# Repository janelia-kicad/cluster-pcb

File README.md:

- [Repository Info](#orgbacf8f6)
- [Images](#org53d800a)
- [Schematic](#org38f91d3)
- [PCB](#org650b85d)
- [Bill of Materials](#org1cf7621)
- [Development](#org0d98822)

    <!-- This file is generated automatically from metadata -->
    <!-- File edits may be overwritten! -->

# Repository Info

-   Project Name: cluster-pcb
-   Synopsis: PCB for each cluster of prisms in the Voigts Lab honeycomb maze.
-   Documentation Version: 2.1.0
-   Pcb Version: 2.1
-   Enclosure Version: 1.0
-   Supplemental BOM Version: 2.1.0
-   Release Date: 2025-05-23
-   Creation Date: 2024-06-28
-   Kicad Version: 9.0
-   License: BSD-3-Clause
-   URL: <https://github.com/janelia-kicad/cluster-pcb>
-   Author: Peter Polidoro
-   Email: peter@polidoro.io
-   Copyright: 2025 Howard Hughes Medical Institute
-   References:
    -   <https://github.com/janelia-kicad/prism-pcb>
    -   [W5500-EVB-Pico](https://docs.wiznet.io/Product/iEthernet/W5500/w5500-evb-pico)

# Images

# Schematic

[./documentation/schematic/cluster-pcb.pdf](./documentation/schematic/cluster-pcb.pdf)

# PCB

# Bill of Materials

## Board

| Item | Synopsis                                  | Manufacturer Part Number | Manufacturer                         | Quantity | Reference(s)                                                                                                                    | Package            |
|---- |----------------------------------------- |------------------------ |------------------------------------ |-------- |------------------------------------------------------------------------------------------------------------------------------- |------------------ |
| 1    | 50V 3.3uF                                 | FS32X335K500EGG          | PSA(Prosperity Dielectrics)          | 1        | C301                                                                                                                            | 1210               |
| 2    | CAP CER 0.1UF 100V X5R                    | GRM155R62A104KE14D       | Murata Electronics                   | 24       | C302 C501 C502 C504 C601 C602 C604 C701 C702 C704 C801 C802 C804 C901 C902 C904 C1001 C1002 C1004 C1101 C1102 C1104 C1201 C1202 | 0402               |
| 3    | CAP CER 1UF 25V X5R                       | GRT155R61E105KE01D       | Murata Electronics                   | 2        | C303 C304                                                                                                                       | 0402               |
| 4    | CAP CER 47UF 10V X5R                      | CGA0805X5R476M100MT      | HRE                                  | 1        | C305                                                                                                                            | 0805               |
| 5    | CAP CER 27pF 50V 5%                       | 0402CG270J500NT          | FH (Guangdong Fenghua Advanced Tech) | 7        | C503 C603 C703 C803 C903 C1003 C1103                                                                                            | 0402               |
| 6    | CAP CER 1UF 35V X5R                       | CL05A105KL5NRNC          | Samsung Electro-Mechanics            | 1        | C1401                                                                                                                           | 0402               |
| 7    | CAP CER 0.22UF 25V X6S                    | GRT155C81E224KE01D       | Murata Electronics                   | 3        | C1402 C1403 C1404                                                                                                               | 0402               |
| 8    | 50V 15A PowerDI-5 Super Barrier Rectifier | SBRT15U50SP5-13          | Diodes Incorporated                  | 1        | D301                                                                                                                            | PowerDI-5          |
| 9    | LED RED CLEAR CHIP SMD                    | APHHS1005SURCK           | Kingbright                           | 1        | D302                                                                                                                            | 0402               |
| 10   | DIODE SCHOTTKY 20V 1A                     | MBR120VLSFT1G            | onsemi                               | 8        | D401 D501 D601 D701 D801 D901 D1001 D1101                                                                                       | SOD-123FL          |
| 11   | CMC 22UH 200MA 2LN 1.2KOHM SMD            | ACT45B-220-2P-TL003      | TDK                                  | 7        | FL501 FL601 FL701 FL801 FL901 FL1001 FL1101                                                                                     | 1812               |
| 12   | USB Type-C 2.0 16P 5A                     | GT-USB-7047C             | G-Switch                             | 7        | J501 J601 J701 J801 J901 J1001 J1101                                                                                            | SMD                |
| 13   | RA73F 2A 2K32 0.1% 5K RL                  | RA73F2A2K32BTD           | TE Connectivity Passive Product      | 1        | R301                                                                                                                            | 0805               |
| 14   | RES SMD 1.8K OHM 5% 100mW                 | ERJ2GEJ182X              | PANASONIC                            | 16       | R401 R402 R505 R506 R605 R606 R705 R706 R805 R806 R905 R906 R1005 R1006 R1105 R1106                                             | 0402               |
| 15   | RES SMD 100 OHM 1% 62.5mW                 | 0402WGF1000TCE           | UNI-ROYAL(Uniroyal Elec)             | 7        | R501 R601 R701 R801 R901 R1001 R1101                                                                                            | 0402               |
| 16   | RES SMD 4.7K OHM 1% 6.25mW                | 0402WGF4701TCE           | UNI-ROYAL(Uniroyal Elec)             | 7        | R502 R602 R702 R802 R902 R1002 R1102                                                                                            | 0402               |
| 17   | RES SMD 1.4K OHM 1% 62.5mW                | RC0402FR-071K4L          | YAGEO                                | 7        | R503 R603 R703 R803 R903 R1003 R1103                                                                                            | 0402               |
| 18   | RES SMD 604 OHM 1% 100mW                  | ERJ2RKF6040X             | PANASONIC                            | 7        | R504 R604 R704 R804 R904 R1004 R1104                                                                                            | 0402               |
| 19   | RES SMD 10K OHM 5% 1/10W                  | ERJ2GEJ103X              | PANASONIC                            | 10       | R1201 R1202 R1203 R1204 R1205 R1206 R1207 R1208 R1209 R1210                                                                     | 0402               |
| 20   | RES SMD 40k OHM 1% 100mW                  | SCR0603F40K              | VO                                   | 2        | R1401 R1402                                                                                                                     | 0603               |
| 21   | SPEAKER 8OHM 700MW                        | KLJ-01304T-08R07W        | KELIKING                             | 1        | SP1401                                                                                                                          |                    |
| 22   | SWITCH SLIDE DIP SPST 0.025A 24V          | SDA08H1SBDR              | C&K                                  | 1        | SW1201                                                                                                                          | SMD                |
| 23   | TERM BLOCK HDR 2POS 90DEG 5.08MM          | 1757242                  | Phoenix Contact                      | 1        | T301                                                                                                                            | Push-Pull P=5.08mm |
| 24   | Pulse Transformer 120uH 1CT:1CT           | FB020G00                 | Dongguan Mentech Optical & Magnetic  | 7        | TR501 TR601 TR701 TR801 TR901 TR1001 TR1101                                                                                     | SMD-6P 3.5x3.2mm   |
| 25   | DC-DC 5V 600mA Output 3-65V Input         | TPSM365R6V5RDNR          | Texas Instruments                    | 1        | U301                                                                                                                            | QFN-11(3.5x4.5)    |
| 26   | SPI Isolator                              | LTC6820HMS#3ZZTRPBF      | Analog Devices                       | 7        | U501 U601 U701 U801 U901 U1001 U1101                                                                                            | MSOP-16            |
| 27   | IC BUFF NON-INVERT 1.65-5.5V              | SN74LVC1G125DRYR         | Texas Instruments                    | 7        | U503 U603 U703 U803 U903 U1003 U1103                                                                                            | USON-6(1x1.5)      |
| 28   | IC XPNDR 400KHZ I2C SMBUS                 | TCA6408ARGTR             | Texas Instruments                    | 1        | U1201                                                                                                                           | QFN-16-EP(3x3)     |
| 29   | IC AMP CLASS AB MONO 1.7W                 | TPA6204A1DRBR            | Texas Instruments                    | 1        | U1401                                                                                                                           | QFN-8-EP(3x3)      |
|      | IC PWR DRIVER N-CHAN 1:1                  |                          | Texas Instruments                    | 7        | U502 U602 U702 U802 U902 U1002 U1102                                                                                            | EMSOP-8-EP         |

## Supplemental

| Item | Synopsis                        | Manufacturer Part Number | Manufacturer    | Quantity | Cost  | Total |
|---- |------------------------------- |------------------------ |--------------- |-------- |----- |----- |
| 1    | TERM BLOCK PLUG 2POS STR 5.08MM | 1758364                  | Phoenix Contact | 1        | 1.63  | 1.63  |
| 2    | CONN FERRULE DIN 16AWG BLACK    | 3200043                  | Phoenix Contact | 4        | 0.14  | 0.56  |
| 3    | POWER CABLE BULK SJT 16/3       | H-137                    | GlobTek, Inc.   | 1        | 2.40  | 2.40  |
| 4    | W5100S-EVB-PICO RP2040 W5100S   | W5100S-EVB-PICO          | WIZnet          | 1        | 9.95  | 9.95  |
| 5    | Supplemental BOM Version: 2.1.0 |                          |                 |          | Total | 14.54 |

# Development

## Install Guix

[Install Guix](https://guix.gnu.org/manual/en/html_node/Binary-Installation.html)

## Generate Output from KiCad

### Remove previous versions

```sh
rm -rf ./documentation/3dmodels/* && rm -rf ./documentation/bom/* && rm -rf ./documentation/fabrication/* && rm -rf ./documentation/pcb/* && rm -rf ./documentation/schematic/*pcb
```

### Images

1.  3D Viewer

    Output directory: ../documentation/pcb
    
    -   pcb.png
    -   top.png
    -   bottom.png
    -   front.png
    -   back.png
    -   left.png
    -   right.png

2.  Trim

        make trimmed-images

3.  Schematic PDF

    File -> Plot
    
    Output directory: ../documentation/schematic
    
    Plot All Pages
    
    -   Output format PDF
    -   Page Size = Schematic size
    -   Plot drawing sheet
    -   Output mode = Color
    -   Color theme = KiCad Default
    -   Default line width = 0.006 in

4.  Schematic SVG

    File -> Plot
    
    Output directory: ../documentation/schematic
    
    Plot All Pages
    
    -   Output format SVG
    -   Page Size = Schematic size
    -   Plot drawing sheet
    -   Output mode = Color
    -   Color theme = Solarized Light
    -   Default line width = 0.012 in

5.  PCB SVG

    Add Edge.Cuts, holes, and dimensions to User.Drawings
    
    File -> Plot
    
    Output directory: ../documentation/pcb
    
    -   Plot format SVG
    -   Include Layers
        -   User.Drawings
        -   F.Silkscreen
        -   B.Silkscreen
        -   F.Fab
        -   B.Fab
    -   Plot on All Layers
        -   Edge.Cuts
    -   Plot footprint values
    -   Plot reference designators
    -   SVG Options
        -   Precision = 4
        -   Output mode = color
    
        make cropped-svg

### Fabrication Files

1.  Gerbers

    File -> Fabrication Outputs -> Gerbers (.gbr)
    
    Output directory: ../documentation/fabrication/gerbers
    
    Include Layers:
    
    -   F.Cu
    -   F.Paste
    -   F.Silks
    -   F.Mask
    -   F.Fab
    -   B.Cu
    -   B.Paste
    -   B.Silks
    -   B.Mask
    -   B.Fab
    -   Edge.Cuts - (contain the board outline/cutouts.)
    -   In1.Cu, In2.Cu … - (needed for 4/6 layer designs.)
    
    Options:
    
    -   Select Plot reference designators, otherwise designators will not appear on silkscreen layers.
    -   Select Check zone fills before plotting
    -   Select Use Protel filename extensions, this is recommended as JLCPCB prefers Protel filename extensions.
    -   Select Subtract soldermask from silkscreen, this ensures no silkscreen on pads.
    -   Coordinate format 4.6 unit mm

2.  Drill and Map Files

    Output directory: ../documentation/fabrication/gerbers
    
    Options:
    
    -   Excellon drill file format
    -   Check Use alternate drill mode for "Oval Holes Drill Mode".
    -   Check Absolute for "Drill Origin".
    -   Check Millimeters for "Drill Units".
    -   Check Decimal format for "Zeros Format".
    -   Gerber X2 map file format
    
    Zip gerber files
    
        zip ./documentation/fabrication/gerbers.zip ./documentation/fabrication/gerbers/*

3.  BOM

    Generate BOM from schematic editor using blank command line to create bom xml file.

4.  POS

    File -> Fabrication Outputs -> Component Placement (.pos)
    
    Output directory: ../documentation/fabrication/
    
    Settings:
    
    -   Format = CSV
    -   Units = Millimeters
    -   Files = Single file for board
    -   Do not use drill/place file origin
    
    Modify pos files:
    
    -   Ref -> Designator
    -   PosX -> Mid X
    -   PosY -> Mid Y
    -   Rot -> Rotation
    -   Side -> Layer

5.  Step

    File -> Export -> Step
    
    Output directory: ../documentation/3dmodels/pcb.step
    
    -   Drill/place file origin
    -   Overwrite old file
    -   Standard Board outline chaining tolerance

## Edit metadata.org

    make metadata-edits

## Tangle metadata.org

    make metadata

## Edit project

    make kicad-edits
    exit

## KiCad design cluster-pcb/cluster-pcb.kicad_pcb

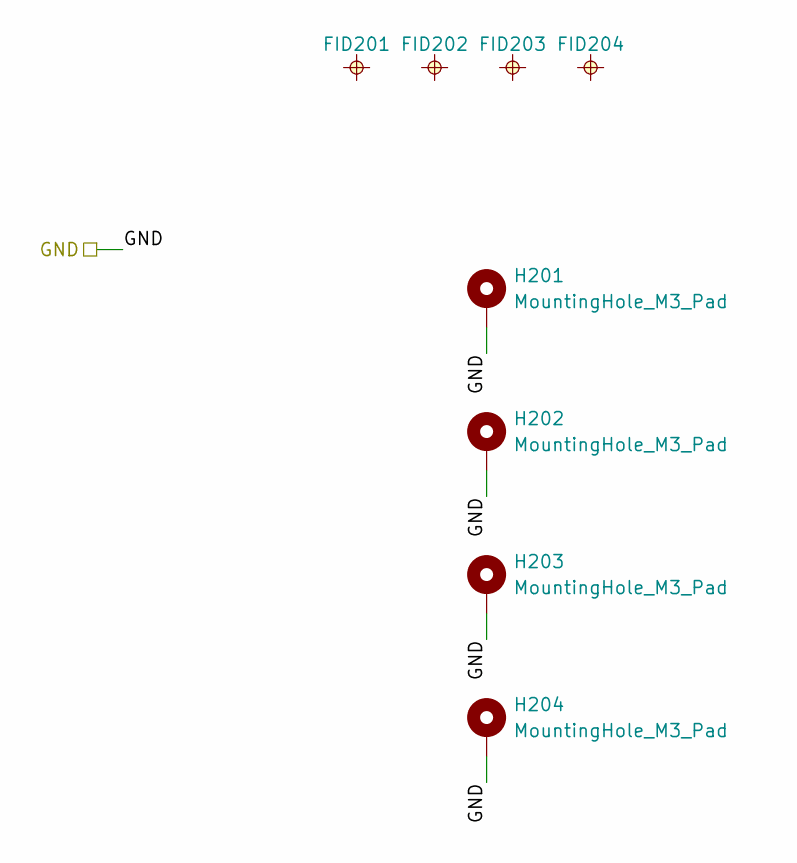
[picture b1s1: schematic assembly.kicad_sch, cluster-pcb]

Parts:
FID201, FID202, FID203, FID204: FIDUCIAL_0.5mm_MASK1mm; FIDUCIAL_0.5mm_Mask1mm
H201, H202, H203, H204: MountingHole_M3_Pad; MountingHole_3.2mm_M3_Pad

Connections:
/GND: H201.1, H202.1, H203.1, H204.1; also elsewhere on the board

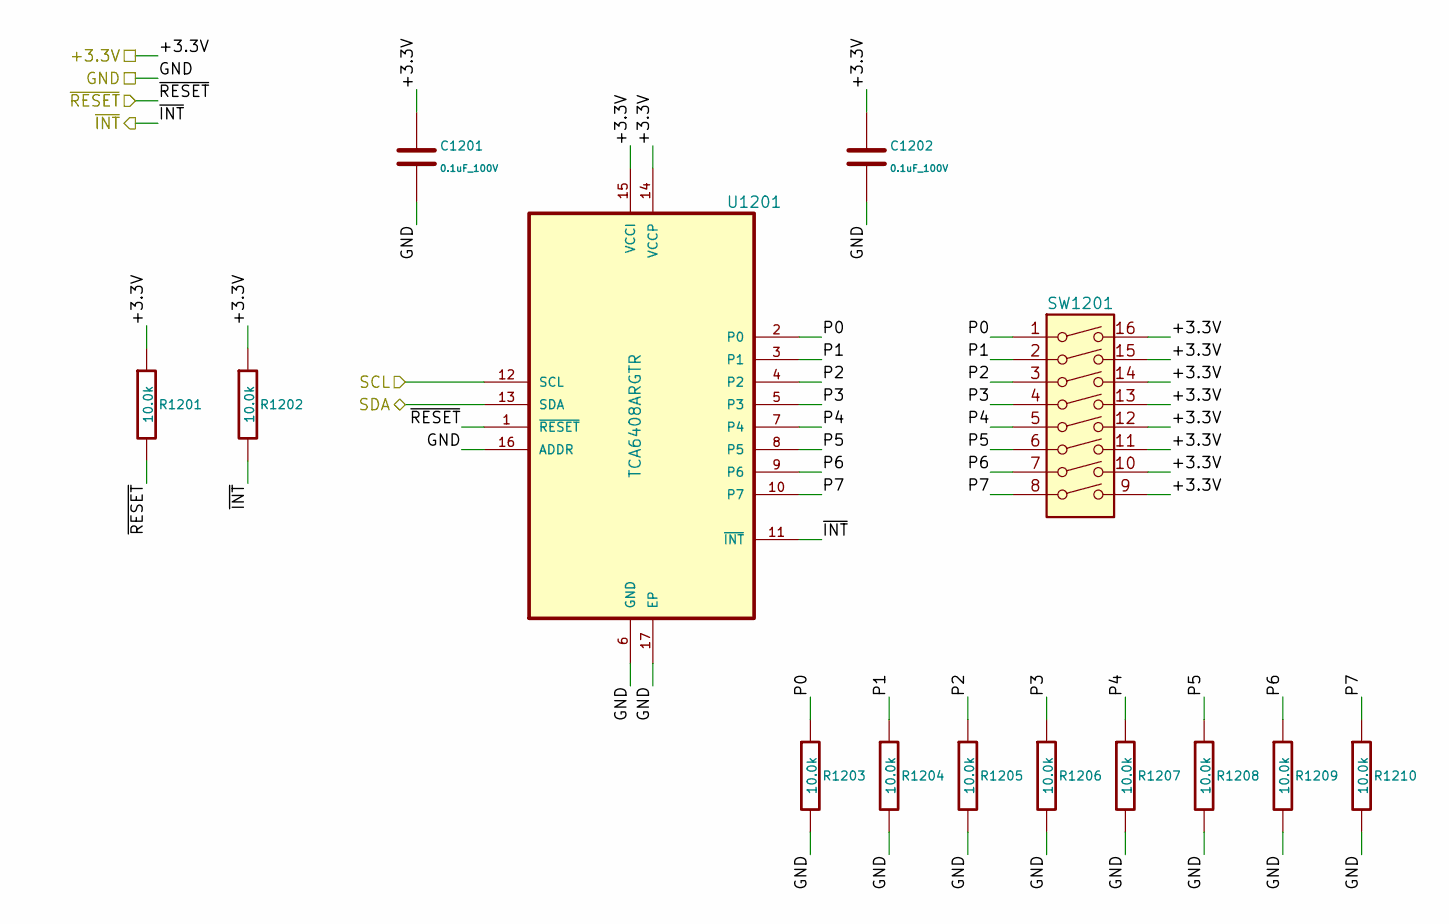
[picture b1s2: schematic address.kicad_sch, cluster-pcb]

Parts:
C1201, C1202: 0.1uF_100V; C_0402_1005Metric; Manufacturer Part Number GRM155R62A104KE14D; LCSC C162178
R1201, R1202, R1203, R1204, R1205, R1206, R1207, R1208, R1209, R1210: 10.0k; R_0402_1005Metric; Manufacturer Part Number ERJ2GEJ103X; LCSC C278577
SW1201: SW_DIP_x08_SDA08H1SBDR; SW_DIP_SPSTx08_Slide_SDA08H1SBDR; Manufacturer Part Number SDA08H1SBDR; LCSC C2799987
U1201: TCA6408ARGTR; QFN50P300X300X100-17N; Manufacturer Part Number TCA6408ARGTR; LCSC C181499

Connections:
/+3.3V: C1201.1, C1202.1, R1201.1, R1202.1, SW1201.9, SW1201.10, SW1201.11, SW1201.12, SW1201.13, SW1201.14, SW1201.15, SW1201.16, U1201.14 (VCCP), U1201.15 (VCCI); also elsewhere on the board
/GND: C1201.2, C1202.2, R1203.2, R1204.2, R1205.2, R1206.2, R1207.2, R1208.2, R1209.2, R1210.2, U1201.6 (GND), U1201.16 (ADDR), U1201.17 (EP); also elsewhere on the board
/SCL: U1201.12 (SCL); also elsewhere on the board
/SDA: U1201.13 (SDA); also elsewhere on the board
/address/P0: R1203.1, SW1201.1, U1201.2 (P0)
/address/P1: R1204.1, SW1201.2, U1201.3 (P1)
/address/P2: R1205.1, SW1201.3, U1201.4 (P2)
/address/P3: R1206.1, SW1201.4, U1201.5 (P3)
/address/P4: R1207.1, SW1201.5, U1201.7 (P4)
/address/P5: R1208.1, SW1201.6, U1201.8 (P5)
/address/P6: R1209.1, SW1201.7, U1201.9 (P6)
/address/P7: R1210.1, SW1201.8, U1201.10 (P7)
/~ADDRESS_INT: R1202.2, U1201.11 (~INT); also elsewhere on the board
/~ADDRESS_RESET: R1201.2, U1201.1 (~RESET); also elsewhere on the board

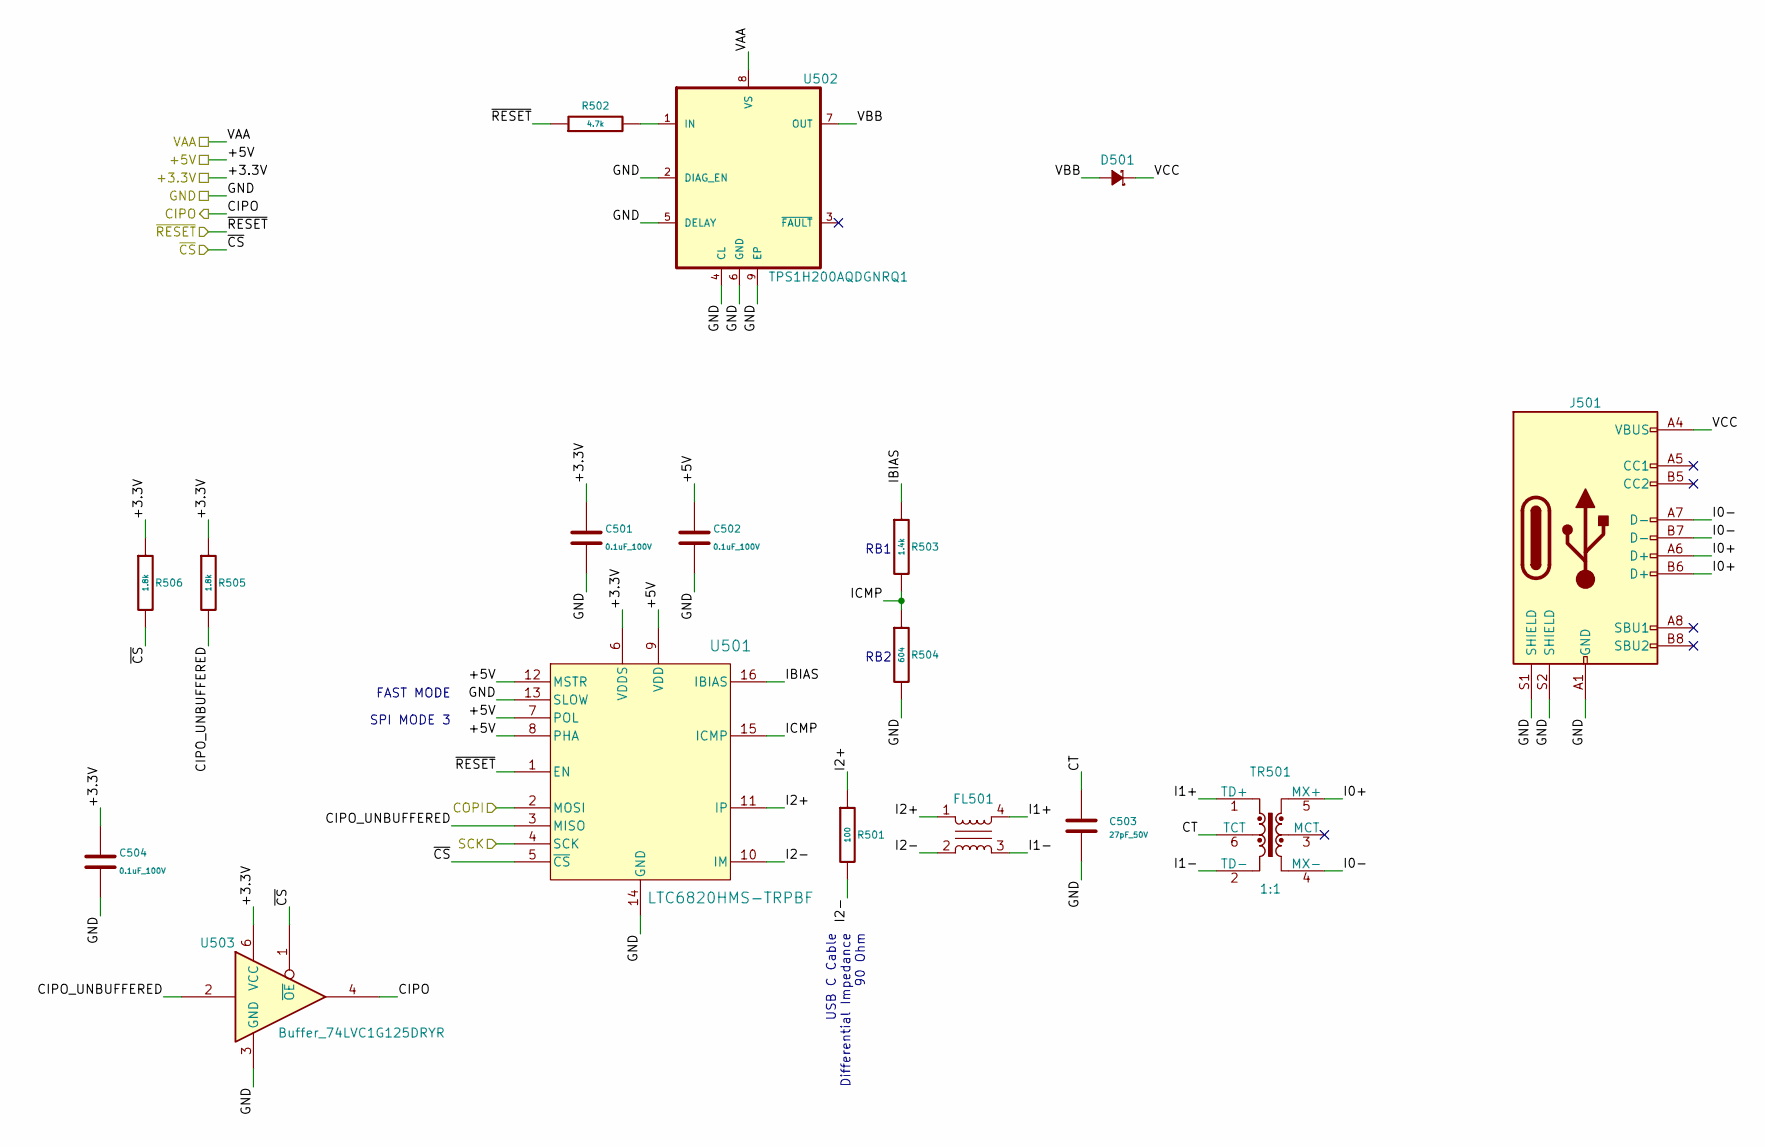
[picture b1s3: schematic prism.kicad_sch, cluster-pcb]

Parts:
C501, C502, C504: 0.1uF_100V; C_0402_1005Metric; Manufacturer Part Number GRM155R62A104KE14D; LCSC C162178
C503: 27pF_50V; C_0402_1005Metric; Manufacturer Part Number 0402CG270J500NT; LCSC C1557
D501: D_SCHOTTKY_20V_1A; SOD-123FL; Manufacturer Part Number DSK36; LCSC C106913
FL501: Choke_CMF_ACT45B-220-2P; SMD_0-2P-TL003_TDK-L; Manufacturer Part Number ACT45B-220-2P-TL003; LCSC C88055
J501: Connector_USB_C_Receptacle_USB2.0_16P_GT-USB-7047C; USB_C_Receptacle_GT-USB-7047C_16P_TopMnt_Horizontal; Manufacturer Part Number GT-USB-7047C; LCSC C963218
R501: 100; R_0402_1005Metric; Manufacturer Part Number 0402WGF1000TCE; LCSC C25076
R502: 4.7k; R_0402_1005Metric; Manufacturer Part Number 0402WGF4701TCE; LCSC C25900
R503: 1.4k; R_0402_1005Metric; Manufacturer Part Number RC0402FR-071K4L; LCSC C375491
R504: 604; R_0402_1005Metric; Manufacturer Part Number ERJ2RKF6040X; LCSC C2076855
R505, R506: 1.8k; R_0402_1005Metric; Manufacturer Part Number ERJ2GEJ182X; LCSC C409855
TR501: 1:1; FB020G00; Manufacturer Part Number FB020G00; LCSC C19673866
U501: LTC6820HMS-TRPBF; MS_05-08-1669_ADI; Manufacturer Part Number LTC6820HMS#3ZZTRPBF; LCSC C514444
U502: TPS1H200AQDGNRQ1; SOP65P490X110-9N; Manufacturer Part Numbn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 TPS1H200AQDGNRQ1; LCSC C2653785
U503: Buffer_74LVC1G125DRYR; DRY6; Manufacturer Part Number SN74LVC1G125DRYR; LCSC C527546

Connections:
/+3.3V: C501.1, C504.1, R505.1, R506.1, U501.6 (VDDS), U503.6 (VCC); also elsewhere on the board
/+5V: C502.1, U501.7 (POL), U501.8 (PHA), U501.9 (VDD), U501.12 (MSTR); also elsewhere on the board
/GND: C501.2, C502.2, C503.2, C504.2, J501.A1 (GND), J501.A12 (GND), J501.B1 (GND), J501.B12 (GND), J501.S1 (SHIELD), J501.S2 (SHIELD), R504.2, U501.13 (SLOW), U501.14 (GND), U502.2 (DIAG_EN), U502.4 (CL), U502.5 (DELAY), U502.6 (GND), U502.9 (EP), U503.3 (GND); also elsewhere on the board
/PRISM_CIPO: U503.4; also elsewhere on the board
/PRISM_COPI: U501.2 (MOSI); also elsewhere on the board
/PRISM_SCK: U501.4 (SCK); also elsewhere on the board
/VAA: U502.8 (VS); also elsewhere on the board
/prism-0/CIPO_UNBUFFERED: R505.2, U501.3 (MISO), U503.2
/prism-0/CT: C503.1, TR501.6 (TCT)
/prism-0/I0+: J501.A6 (D+), J501.B6 (D+), TR501.5 (MX+)
/prism-0/I0-: J501.A7 (D-), J501.B7 (D-), TR501.4 (MX-)
/prism-0/I1+: FL501.4, TR501.1 (TD+)
/prism-0/I1-: FL501.3, TR501.2 (TD-)
/prism-0/I2+: FL501.1, R501.1, U501.11 (IP)
/prism-0/I2-: FL501.2, R501.2, U501.10 (IM)
/prism-0/IBIAS: R503.1, U501.16 (IBIAS)
/prism-0/ICMP: R503.2, R504.1, U501.15 (ICMP)
/prism-0/VBB: D501.2 (A), U502.7 (OUT)
/prism-0/VCC: D501.1 (K), J501.A4 (VBUS), J501.A9 (VBUS), J501.B4 (VBUS), J501.B9 (VBUS)
/~PRISMS_RESET: R502.1, U501.1 (EN); also elsewhere on the board
/~PRISM_CS_0: R506.2, U501.5 (~CS), U503.1 (~OE); also elsewhere on the board
unnamed: R502.2, U502.1 (IN)

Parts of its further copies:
C601, C602, C604, C701, C702, C704, C801, C802, C804, C901, C902, C904, C1001, C1002, C1004, C1101, C1102, C1104: 0.1uF_100V; C_0402_1005Metric; Manufacturer Part Number GRM155R62A104KE14D; LCSC C162178
C603, C703, C803, C903, C1003, C1103: 27pF_50V; C_0402_1005Metric; Manufacturer Part Number 0402CG270J500NT; LCSC C1557
D601, D701, D801, D901, D1001, D1101: D_SCHOTTKY_20V_1A; SOD-123FL; Manufacturer Part Number DSK36; LCSC C106913
FL601, FL701, FL801, FL901, FL1001, FL1101: Choke_CMF_ACT45B-220-2P; SMD_0-2P-TL003_TDK-L; Manufacturer Part Number ACT45B-220-2P-TL003; LCSC C88055
J601, J701, J801, J901, J1001, J1101: Connector_USB_C_Receptacle_USB2.0_16P_GT-USB-7047C; USB_C_Receptacle_GT-USB-7047C_16P_TopMnt_Horizontal; Manufacturer Part Number GT-USB-7047C; LCSC C963218
R601, R701, R801, R901, R1001, R1101: 100; R_0402_1005Metric; Manufacturer Part Number 0402WGF1000TCE; LCSC C25076
R602, R702, R802, R902, R1002, R1102: 4.7k; R_0402_1005Metric; Manufacturer Part Number 0402WGF4701TCE; LCSC C25900
R603, R703, R803, R903, R1003, R1103: 1.4k; R_0402_1005Metric; Manufacturer Part Number RC0402FR-071K4L; LCSC C375491
R604, R704, R804, R904, R1004, R1104: 604; R_0402_1005Metric; Manufacturer Part Number ERJ2RKF6040X; LCSC C2076855
R605, R606, R705, R706, R805, R806, R905, R906, R1005, R1006, R1105, R1106: 1.8k; R_0402_1005Metric; Manufacturer Part Number ERJ2GEJ182X; LCSC C409855
TR601, TR701, TR801, TR901, TR1001, TR1101: 1:1; FB020G00; Manufacturer Part Number FB020G00; LCSC C19673866
U601, U701, U801, U901, U1001, U1101: LTC6820HMS-TRPBF; MS_05-08-1669_ADI; Manufacturer Part Number LTC6820HMS#3ZZTRPBF; LCSC C514444
U602, U702, U802, U902, U1002, U1102: TPS1H200AQDGNRQ1; SOP65P490X110-9N; Manufacturer Part Numbn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 TPS1H200AQDGNRQ1; LCSC C2653785
U603, U703, U803, U903, U1003, U1103: Buffer_74LVC1G125DRYR; DRY6; Manufacturer Part Number SN74LVC1G125DRYR; LCSC C527546

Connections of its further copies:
/+3.3V: C601.1, C604.1, C701.1, C704.1, C801.1, C804.1, C901.1, C904.1, C1001.1, C1004.1, C1101.1, C1104.1, R605.1, R606.1, R705.1, R706.1, R805.1, R806.1, R905.1, R906.1, R1005.1, R1006.1, R1105.1, R1106.1, U601.6 (VDDS), U603.6 (VCC), U701.6 (VDDS), U703.6 (VCC), U801.6 (VDDS), U803.6 (VCC), U901.6 (VDDS), U903.6 (VCC), U1001.6 (VDDS), U1003.6 (VCC), U1101.6 (VDDS), U1103.6 (VCC); also elsewhere on the board
/+5V: C602.1, C702.1, C802.1, C902.1, C1002.1, C1102.1, U601.7 (POL), U601.8 (PHA), U601.9 (VDD), U601.12 (MSTR), U701.7 (POL), U701.8 (PHA), U701.9 (VDD), U701.12 (MSTR), U801.7 (POL), U801.8 (PHA), U801.9 (VDD), U801.12 (MSTR), U901.7 (POL), U901.8 (PHA), U901.9 (VDD), U901.12 (MSTR), U1001.7 (POL), U1001.8 (PHA), U1001.9 (VDD), U1001.12 (MSTR), U1101.7 (POL), U1101.8 (PHA), U1101.9 (VDD), U1101.12 (MSTR); also elsewhere on the board
/GND: C601.2, C602.2, C603.2, C604.2, C701.2, C702.2, C703.2, C704.2, C801.2, C802.2, C803.2, C804.2, C901.2, C902.2, C903.2, C904.2, C1001.2, C1002.2, C1003.2, C1004.2, C1101.2, C1102.2, C1103.2, C1104.2, J601.A1 (GND), J601.A12 (GND), J601.B1 (GND), J601.B12 (GND), J601.S1 (SHIELD), J601.S2 (SHIELD), J701.A1 (GND), J701.A12 (GND), J701.B1 (GND), J701.B12 (GND), J701.S1 (SHIELD), J701.S2 (SHIELD), J801.A1 (GND), J801.A12 (GND), J801.B1 (GND), J801.B12 (GND), J801.S1 (SHIELD), J801.S2 (SHIELD), J901.A1 (GND), J901.A12 (GND), J901.B1 (GND), J901.B12 (GND), J901.S1 (SHIELD), J901.S2 (SHIELD), J1001.A1 (GND), J1001.A12 (GND), J1001.B1 (GND), J1001.B12 (GND), J1001.S1 (SHIELD), J1001.S2 (SHIELD), J1101.A1 (GND), J1101.A12 (GND), J1101.B1 (GND), J1101.B12 (GND), J1101.S1 (SHIELD), J1101.S2 (SHIELD), R604.2, R704.2, R804.2, R904.2, R1004.2, R1104.2, U601.13 (SLOW), U601.14 (GND), U602.2 (DIAG_EN), U602.4 (CL), U602.5 (DELAY), U602.6 (GND), U602.9 (EP), U603.3 (GND), U701.13 (SLOW), U701.14 (GND), U702.2 (DIAG_EN), U702.4 (CL), U702.5 (DELAY), U702.6 (GND), U702.9 (EP), U703.3 (GND), U801.13 (SLOW), U801.14 (GND), U802.2 (DIAG_EN), U802.4 (CL), U802.5 (DELAY), U802.6 (GND), U802.9 (EP), U803.3 (GND), U901.13 (SLOW), U901.14 (GND), U902.2 (DIAG_EN), U902.4 (CL), U902.5 (DELAY), U902.6 (GND), U902.9 (EP), U903.3 (GND), U1001.13 (SLOW), U1001.14 (GND), U1002.2 (DIAG_EN), U1002.4 (CL), U1002.5 (DELAY), U1002.6 (GND), U1002.9 (EP), U1003.3 (GND), U1101.13 (SLOW), U1101.14 (GND), U1102.2 (DIAG_EN), U1102.4 (CL), U1102.5 (DELAY), U1102.6 (GND), U1102.9 (EP), U1103.3 (GND); also elsewhere on the board
/PRISM_CIPO: U603.4, U703.4, U803.4, U903.4, U1003.4, U1103.4; also elsewhere on the board
/PRISM_COPI: U601.2 (MOSI), U701.2 (MOSI), U801.2 (MOSI), U901.2 (MOSI), U1001.2 (MOSI), U1101.2 (MOSI); also elsewhere on the board
/PRISM_SCK: U601.4 (SCK), U701.4 (SCK), U801.4 (SCK), U901.4 (SCK), U1001.4 (SCK), U1101.4 (SCK); also elsewhere on the board
/VAA: U602.8 (VS), U702.8 (VS), U802.8 (VS), U902.8 (VS), U1002.8 (VS), U1102.8 (VS); also elsewhere on the board
/prism-1/CIPO_UNBUFFERED: R605.2, U601.3 (MISO), U603.2
/prism-1/CT: C603.1, TR601.6 (TCT)
/prism-1/I0+: J601.A6 (D+), J601.B6 (D+), TR601.5 (MX+)
/prism-1/I0-: J601.A7 (D-), J601.B7 (D-), TR601.4 (MX-)
/prism-1/I1+: FL601.4, TR601.1 (TD+)
/prism-1/I1-: FL601.3, TR601.2 (TD-)
/prism-1/I2+: FL601.1, R601.1, U601.11 (IP)
/prism-1/I2-: FL601.2, R601.2, U601.10 (IM)
/prism-1/IBIAS: R603.1, U601.16 (IBIAS)
/prism-1/ICMP: R603.2, R604.1, U601.15 (ICMP)
/prism-1/VBB: D601.2 (A), U602.7 (OUT)
/prism-1/VCC: D601.1 (K), J601.A4 (VBUS), J601.A9 (VBUS), J601.B4 (VBUS), J601.B9 (VBUS)
/prism-2/CIPO_UNBUFFERED: R705.2, U701.3 (MISO), U703.2
/prism-2/CT: C703.1, TR701.6 (TCT)
/prism-2/I0+: J701.A6 (D+), J701.B6 (D+), TR701.5 (MX+)
/prism-2/I0-: J701.A7 (D-), J701.B7 (D-), TR701.4 (MX-)
/prism-2/I1+: FL701.4, TR701.1 (TD+)
/prism-2/I1-: FL701.3, TR701.2 (TD-)
/prism-2/I2+: FL701.1, R701.1, U701.11 (IP)
/prism-2/I2-: FL701.2, R701.2, U701.10 (IM)
/prism-2/IBIAS: R703.1, U701.16 (IBIAS)
/prism-2/ICMP: R703.2, R704.1, U701.15 (ICMP)
/prism-2/VBB: D701.2 (A), U702.7 (OUT)
/prism-2/VCC: D701.1 (K), J701.A4 (VBUS), J701.A9 (VBUS), J701.B4 (VBUS), J701.B9 (VBUS)
/prism-3/CIPO_UNBUFFERED: R805.2, U801.3 (MISO), U803.2
/prism-3/CT: C803.1, TR801.6 (TCT)
/prism-3/I0+: J801.A6 (D+), J801.B6 (D+), TR801.5 (MX+)
/prism-3/I0-: J801.A7 (D-), J801.B7 (D-), TR801.4 (MX-)
/prism-3/I1+: FL801.4, TR801.1 (TD+)
/prism-3/I1-: FL801.3, TR801.2 (TD-)
/prism-3/I2+: FL801.1, R801.1, U801.11 (IP)
/prism-3/I2-: FL801.2, R801.2, U801.10 (IM)
/prism-3/IBIAS: R803.1, U801.16 (IBIAS)
/prism-3/ICMP: R803.2, R804.1, U801.15 (ICMP)
/prism-3/VBB: D801.2 (A), U802.7 (OUT)
/prism-3/VCC: D801.1 (K), J801.A4 (VBUS), J801.A9 (VBUS), J801.B4 (VBUS), J801.B9 (VBUS)
/prism-4/CIPO_UNBUFFERED: R1005.2, U1001.3 (MISO), U1003.2
/prism-4/CT: C1003.1, TR1001.6 (TCT)
/prism-4/I0+: J1001.A6 (D+), J1001.B6 (D+), TR1001.5 (MX+)
/prism-4/I0-: J1001.A7 (D-), J1001.B7 (D-), TR1001.4 (MX-)
/prism-4/I1+: FL1001.4, TR1001.1 (TD+)
/prism-4/I1-: FL1001.3, TR1001.2 (TD-)
/prism-4/I2+: FL1001.1, R1001.1, U1001.11 (IP)
/prism-4/I2-: FL1001.2, R1001.2, U1001.10 (IM)
/prism-4/IBIAS: R1003.1, U1001.16 (IBIAS)
/prism-4/ICMP: R1003.2, R1004.1, U1001.15 (ICMP)
/prism-4/VBB: D1001.2 (A), U1002.7 (OUT)
/prism-4/VCC: D1001.1 (K), J1001.A4 (VBUS), J1001.A9 (VBUS), J1001.B4 (VBUS), J1001.B9 (VBUS)
/prism-5/CIPO_UNBUFFERED: R905.2, U901.3 (MISO), U903.2
/prism-5/CT: C903.1, TR901.6 (TCT)
/prism-5/I0+: J901.A6 (D+), J901.B6 (D+), TR901.5 (MX+)
/prism-5/I0-: J901.A7 (D-), J901.B7 (D-), TR901.4 (MX-)
/prism-5/I1+: FL901.4, TR901.1 (TD+)
/prism-5/I1-: FL901.3, TR901.2 (TD-)
/prism-5/I2+: FL901.1, R901.1, U901.11 (IP)
/prism-5/I2-: FL901.2, R901.2, U901.10 (IM)
/prism-5/IBIAS: R903.1, U901.16 (IBIAS)
/prism-5/ICMP: R903.2, R904.1, U901.15 (ICMP)
/prism-5/VBB: D901.2 (A), U902.7 (OUT)
/prism-5/VCC: D901.1 (K), J901.A4 (VBUS), J901.A9 (VBUS), J901.B4 (VBUS), J901.B9 (VBUS)
/prism-6/CIPO_UNBUFFERED: R1105.2, U1101.3 (MISO), U1103.2
/prism-6/CT: C1103.1, TR1101.6 (TCT)
/prism-6/I0+: J1101.A6 (D+), J1101.B6 (D+), TR1101.5 (MX+)
/prism-6/I0-: J1101.A7 (D-), J1101.B7 (D-), TR1101.4 (MX-)
/prism-6/I1+: FL1101.4, TR1101.1 (TD+)
/prism-6/I1-: FL1101.3, TR1101.2 (TD-)
/prism-6/I2+: FL1101.1, R1101.1, U1101.11 (IP)
/prism-6/I2-: FL1101.2, R1101.2, U1101.10 (IM)
/prism-6/IBIAS: R1103.1, U1101.16 (IBIAS)
/prism-6/ICMP: R1103.2, R1104.1, U1101.15 (ICMP)
/prism-6/VBB: D1101.2 (A), U1102.7 (OUT)
/prism-6/VCC: D1101.1 (K), J1101.A4 (VBUS), J1101.A9 (VBUS), J1101.B4 (VBUS), J1101.B9 (VBUS)
/~PRISMS_RESET: R602.1, R702.1, R802.1, R902.1, R1002.1, R1102.1, U601.1 (EN), U701.1 (EN), U801.1 (EN), U901.1 (EN), U1001.1 (EN), U1101.1 (EN); also elsewhere on the board
/~PRISM_CS_1: R606.2, U601.5 (~CS), U603.1 (~OE); also elsewhere on the board
/~PRISM_CS_2: R706.2, U701.5 (~CS), U703.1 (~OE); also elsewhere on the board
/~PRISM_CS_3: R806.2, U801.5 (~CS), U803.1 (~OE); also elsewhere on the board
/~PRISM_CS_4: R1006.2, U1001.5 (~CS), U1003.1 (~OE); also elsewhere on the board
/~PRISM_CS_5: R906.2, U901.5 (~CS), U903.1 (~OE); also elsewhere on the board
/~PRISM_CS_6: R1106.2, U1101.5 (~CS), U1103.1 (~OE); also elsewhere on the board
unnamed: R602.2, U602.1 (IN)
unnamed: R702.2, U702.1 (IN)
unnamed: R802.2, U802.1 (IN)
unnamed: R902.2, U902.1 (IN)
unnamed: R1002.2, U1002.1 (IN)
unnamed: R1102.2, U1102.1 (IN)

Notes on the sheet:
RB1
RB2
USB C Cable Differential Impedance 90 Ohm
SPI MODE 3
FAST MODE

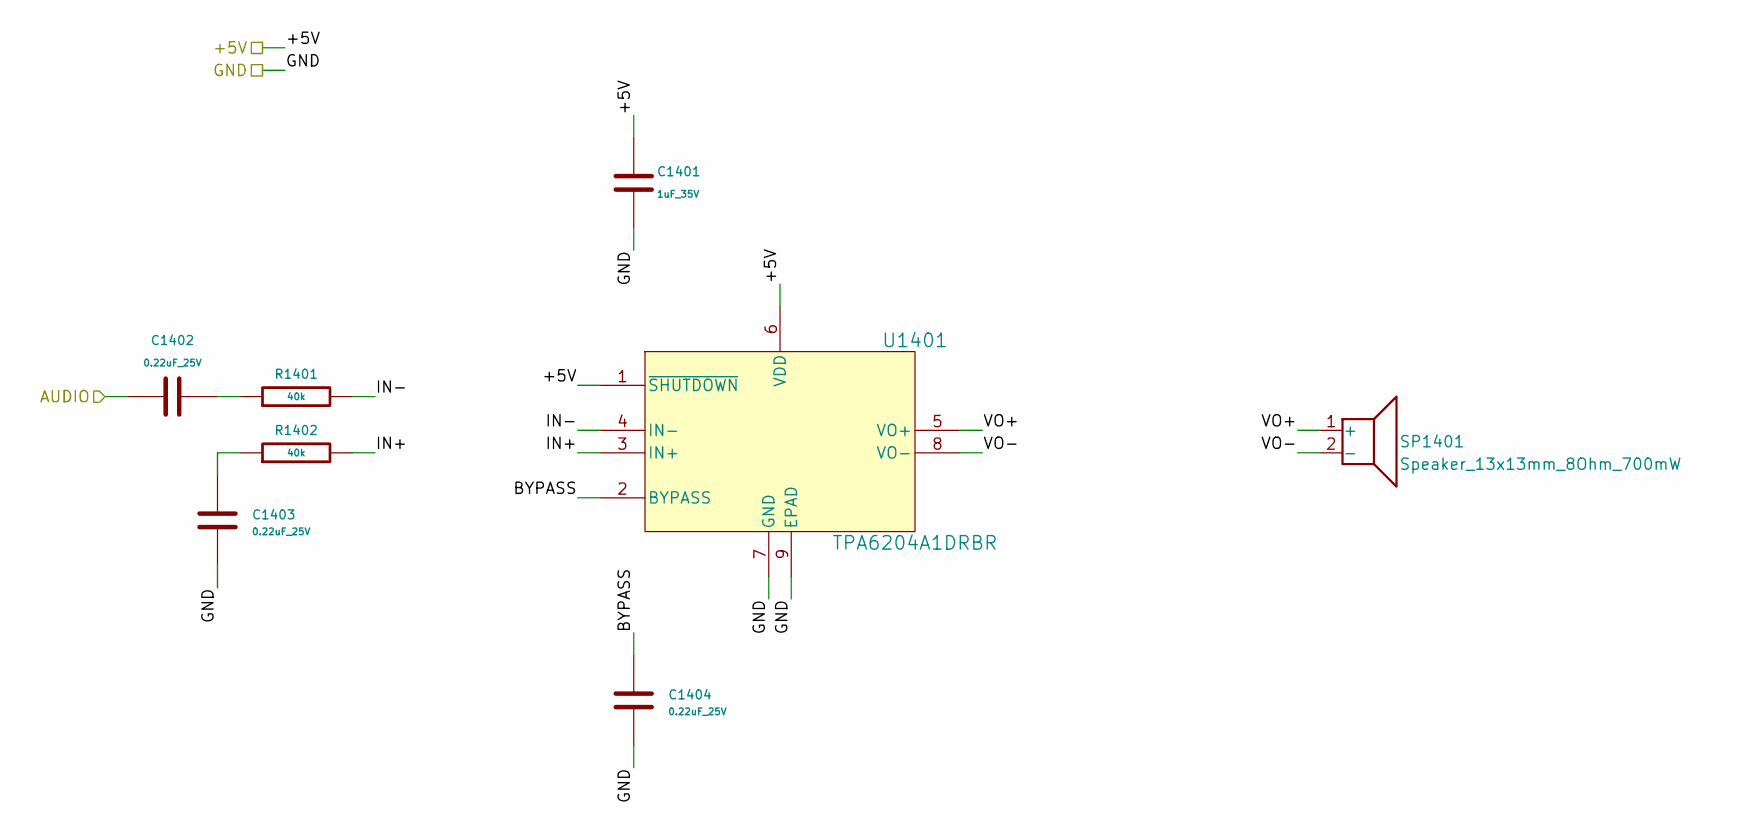
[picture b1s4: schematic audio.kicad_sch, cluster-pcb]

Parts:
C1401: 1uF_35V; C_0402_1005Metric; Manufacturer Part Number CL05A105KL5NRNC; LCSC C307413
C1402, C1403, C1404: 0.22uF_25V; C_0402_1005Metric; Manufacturer Part Number GRT155C81E224KE01D; LCSC C126623
R1401, R1402: 40k; R_0603_1608Metric; Manufacturer Part Number SCR0603F40K; LCSC C3016445
SP1401: Speaker_13x13mm_8Ohm_700mW; Speaker_13x13mm_KLJ-01304T-08R07W; Manufacturer Part Number KLJ-01304T-08R07W; LCSC C18186315
U1401: TPA6204A1DRBR; DRB8_1P75X1P5; Manufacturer Part Number TPA6204A1DRBR; LCSC C12400

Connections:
/+5V: C1401.1, U1401.1 (~SHUTDOWN), U1401.6 (VDD); also elsewhere on the board
/AUDIO: C1402.1; also elsewhere on the board
/GND: C1401.2, C1403.1, C1404.1, U1401.7 (GND), U1401.9 (EPAD); also elsewhere on the board
/audio/BYPASS: C1404.2, U1401.2 (BYPASS)
/audio/IN+: R1402.2, U1401.3 (IN+)
/audio/IN-: R1401.2, U1401.4 (IN-)
/audio/VO+: SP1401.1 (+), U1401.5 (VO+)
/audio/VO-: SP1401.2 (-), U1401.8 (VO-)
unnamed: C1402.2, R1401.1
unnamed: C1403.2, R1402.1

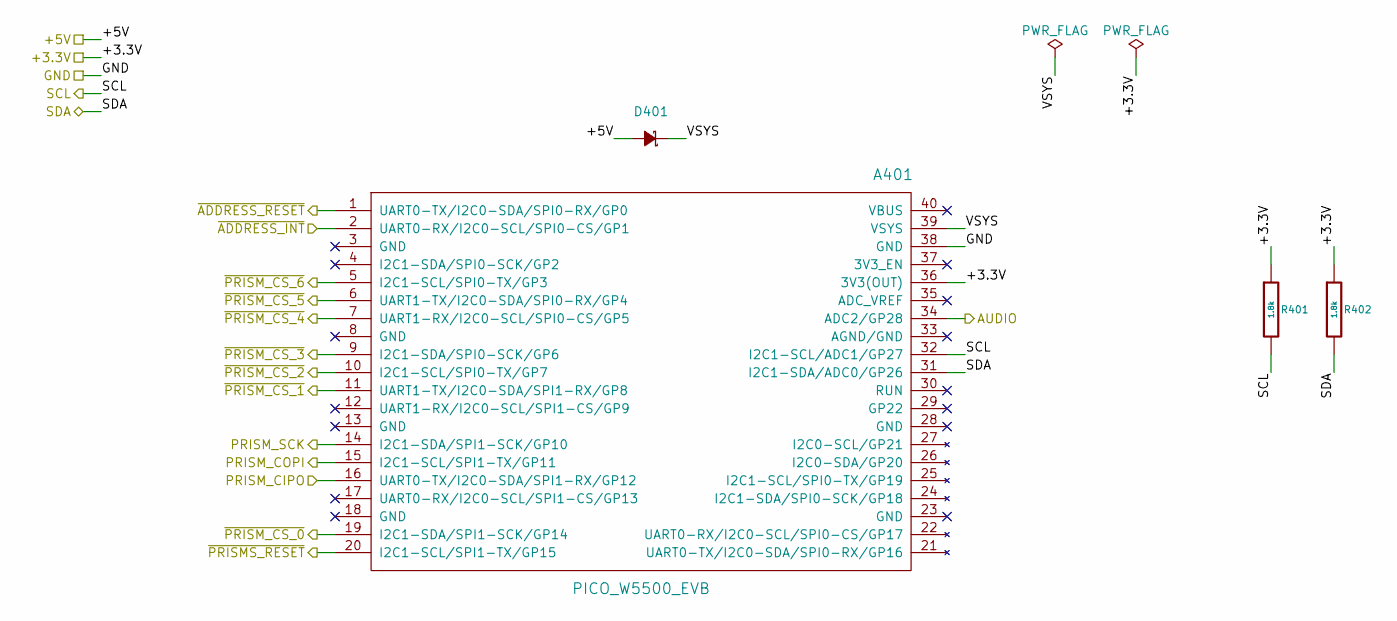
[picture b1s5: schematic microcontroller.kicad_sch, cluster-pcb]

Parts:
A401: PICO_W5500_EVB; Pico-W5500-EVB_Header_Holes
D401: D_SCHOTTKY_20V_1A; SOD-123FL; Manufacturer Part Number MBR120VLSFT1G; LCSC C223608
R401, R402: 1.8k; R_0402_1005Metric; Manufacturer Part Number ERJ2GEJ182X; LCSC C409855

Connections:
/+3.3V: A401.36 (3V3(OUT)), R401.1, R402.1; also elsewhere on the board
/+5V: D401.2 (A); also elsewhere on the board
/AUDIO: A401.34 (ADC2/GP28); also elsewhere on the board
/GND: A401.38 (GND); also elsewhere on the board
/PRISM_CIPO: A401.16 (UART0-TX/I2C0-SDA/SPI1-RX/GP12); also elsewhere on the board
/PRISM_COPI: A401.15 (I2C1-SCL/SPI1-TX/GP11); also elsewhere on the board
/PRISM_SCK: A401.14 (I2C1-SDA/SPI1-SCK/GP10); also elsewhere on the board
/SCL: A401.32 (I2C1-SCL/ADC1/GP27), R401.2; also elsewhere on the board
/SDA: A401.31 (I2C1-SDA/ADC0/GP26), R402.2; also elsewhere on the board
/microcontroller/VSYS: A401.39 (VSYS), D401.1 (K)
/~ADDRESS_INT: A401.2 (UART0-RX/I2C0-SCL/SPI0-CS/GP1); also elsewhere on the board
/~ADDRESS_RESET: A401.1 (UART0-TX/I2C0-SDA/SPI0-RX/GP0); also elsewhere on the board
/~PRISMS_RESET: A401.20 (I2C1-SCL/SPI1-TX/GP15); also elsewhere on the board
/~PRISM_CS_0: A401.19 (I2C1-SDA/SPI1-SCK/GP14); also elsewhere on the board
/~PRISM_CS_1: A401.11 (UART1-TX/I2C0-SDA/SPI1-RX/GP8); also elsewhere on the board
/~PRISM_CS_2: A401.10 (I2C1-SCL/SPI0-TX/GP7); also elsewhere on the board
/~PRISM_CS_3: A401.9 (I2C1-SDA/SPI0-SCK/GP6); also elsewhere on the board
/~PRISM_CS_4: A401.7 (UART1-RX/I2C0-SCL/SPI0-CS/GP5); also elsewhere on the board
/~PRISM_CS_5: A401.6 (UART1-TX/I2C0-SDA/SPI0-RX/GP4); also elsewhere on the board
/~PRISM_CS_6: A401.5 (I2C1-SCL/SPI0-TX/GP3); also elsewhere on the board

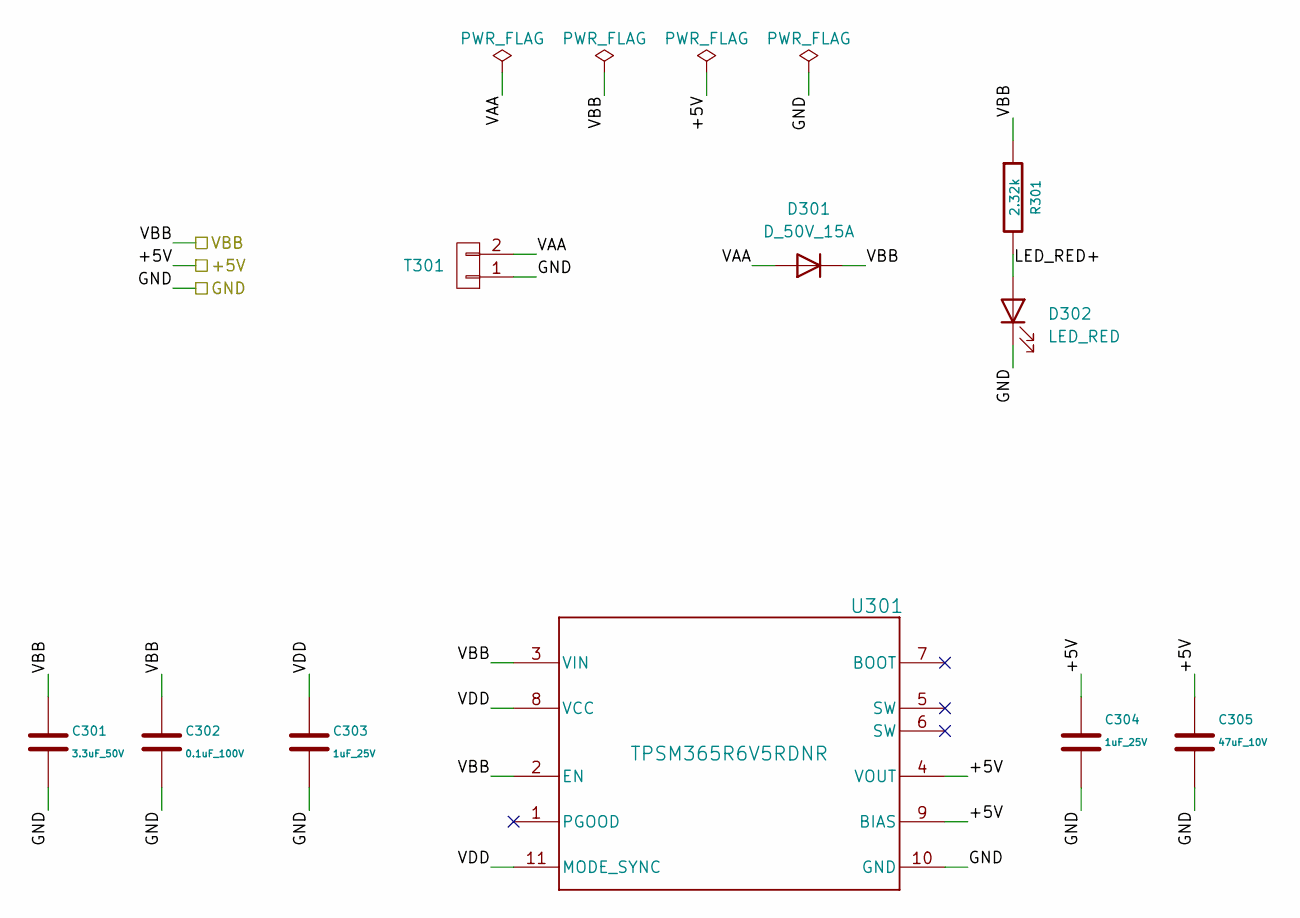
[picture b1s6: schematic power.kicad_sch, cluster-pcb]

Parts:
C301: 3.3uF_50V; C_1210_3225Metric; Manufacturer Part Number FS32X335K500EGG; LCSC C1021610
C302: 0.1uF_100V; C_0402_1005Metric; Manufacturer Part Number GRM155R62A104KE14D; LCSC C162178
C303, C304: 1uF_25V; C_0402_1005Metric; Manufacturer Part Number GRT155R61E105KE01D; LCSC C711085
C305: 47uF_10V; C_0805_2012Metric; Manufacturer Part Number CGA0805X5R476M100MT; LCSC C6119904
D301: D_50V_15A; POWERDI5_DIO; Manufacturer Part Number SBRT15U50SP5-13; LCSC C211388
D302: LED_RED; LED_0402-1005_KNB; Manufacturer Part Number APHHS1005SURCK; LCSC C2852592
R301: 2.32k; R_0805_2012Metric; Manufacturer Part Number RA73F2A2K32BTD; LCSC C3961061
T301: TERM_BLK_HDR_2POS_90DEG_0.2IN; PHOENIX_1757242; Manufacturer Part Number 1757242; LCSC C90074
U301: TPSM365R6V5RDNR; RDN0011A-MFG; Manufacturer Part Number TPSM365R6V5RDNR; LCSC C19078014

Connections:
/+5V: C304.1, C305.1, U301.4 (VOUT), U301.9 (BIAS); also elsewhere on the board
/GND: C301.2, C302.2, C303.2, C304.2, C305.2, D302.1 (K), T301.1, U301.10 (GND); also elsewhere on the board
/VAA: C301.1, C302.1, D301.1 (K), R301.1, U301.2 (EN), U301.3 (VIN); also elsewhere on the board
/power/LED_RED+: D302.2 (A), R301.2
/power/VAA: D301.2 (A), T301.2
/power/VDD: C303.1, U301.8 (VCC), U301.11 (MODE_SYNC)
